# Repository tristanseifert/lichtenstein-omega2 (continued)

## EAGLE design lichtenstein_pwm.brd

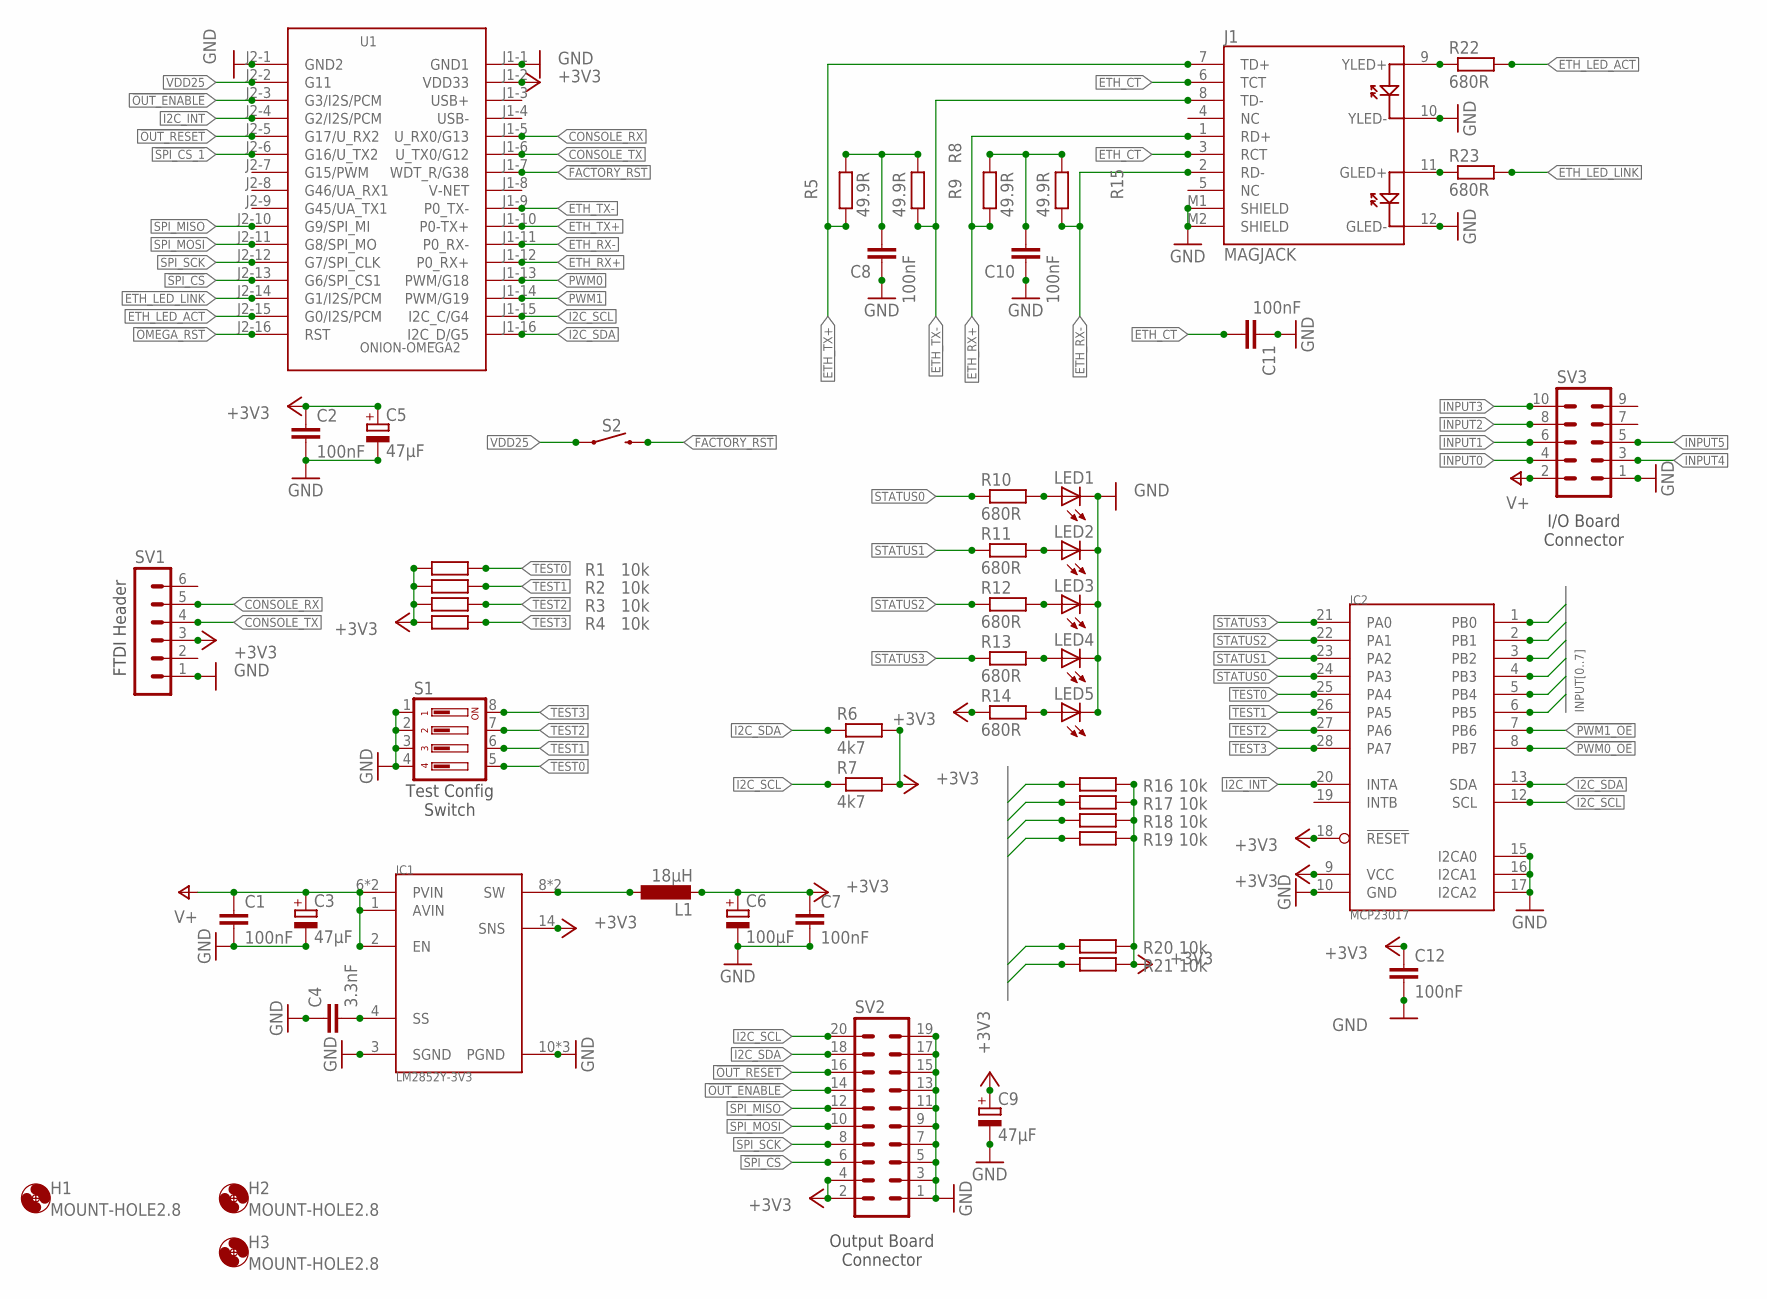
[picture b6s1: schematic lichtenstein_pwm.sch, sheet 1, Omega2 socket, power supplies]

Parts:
C1, C2, C7, C8, C10, C11, C12: 100nF; C0805; MOUSER 710-885012207072
C3, C5: 47µF; CT7343; MOUSER 581-TAJD476M016RNJV
C4: 3.3nF; C0805; MOUSER 710-885012207089
C6: 100µF; CT7343; MOUSER 581-NOSD107M006
C9: 47µF; SMC_D; MOUSER 581-TAJD476M016RNJV
H1, H2, H3: MOUNT-HOLE2.8; 2,8
IC1: LM2852Y-3V3; HTSSOP14
IC2: MCP23017; SSOP28
J1: MAGJACK
L1: 18µH; SRR1050A
LED1: LEDCHIPLED_1206; CHIPLED_1206; MOUSER 604-APTR3216SRCPRV
LED2, LED3, LED4, LED5: LEDCHIPLED_1206; CHIPLED_1206; MOUSER 604-APTR3216SGC
R1, R2, R3, R4, R16, R17, R18, R19, R20, R21: 10k; M0805; MOUSER 652-CR0805FX-1002ELF
R5, R9, R15: 49.9R; M0805; MOUSER 652-CR0805FX-49R9ELF
R6, R7: 4k7; M0805; MOUSER 652-CR0805-FX4701GLF
R8: 49.9R; M0805; MOUSER 652-CR0805-FX4701GLF
R10, R11, R12, R13, R14, R22, R23: 680R; M0805; MOUSER 652-CR0805-FX6800GLF
S1: 219-04; CTS-219-04; MOUSER 774-219-4LPS
S2: MOMENTARY-SWITCH-SPST-PTH-6.0MM; TACTILE_SWITCH_PTH_6.0MM; MOUSER 612-TL1105B
SV1: MA06-1
SV2: MA10-2; MOUSER 517-30320-6002
SV3: MA05-2; MOUSER 517-30310-6002
U1: ONION-OMEGA2; ONION-2MM-2X16; MOUSER 353-OM-O2P

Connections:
!FACTORY_RST: S2.3 (2), U1.J1-7 (WDT_R/G38)
!OMEGA_RST: U1.J2-16 (RST)
!OUT_ENABLE: SV2.14, U1.J2-3 (G3/I2S/PCM)
!OUT_RESET: SV2.16, U1.J2-5 (G17/U_RX2)
!PWM0_OE: IC2.8 (PB7); also elsewhere on the board
!PWM1_OE: IC2.7 (PB6); also elsewhere on the board
!SPI_CS: SV2.6, U1.J2-13 (G6/SPI_CS1)
!SPI_CS_1: U1.J2-6 (G16/U_TX2)
+3V3: C2.1, C5.+, C6.+, C7.1, C9.+, C12.1, IC1.14 (SNS), IC2.9 (VCC), IC2.18 (!RESET), L1.P$2 (2), R1.1, R2.1, R3.1, R4.1, R6.2, R7.2, R14.1, R16.2, R17.2, R18.2, R19.2, R20.2, R21.2, SV1.3, SV2.2, SV2.4, U1.J1-2 (VDD33); also elsewhere on the board
CONSOLE_RX: SV1.5, U1.J1-5 (U_RX0/G13)
CONSOLE_TX: SV1.4, U1.J1-6 (U_TX0/G12)
ETH_CT: C11.2, J1.3 (RCT), J1.6 (TCT)
ETH_LED_ACT: R22.2, U1.J2-15 (G0/I2S/PCM)
ETH_LED_LINK: R23.2, U1.J2-14 (G1/I2S/PCM)
ETH_RX+: J1.1 (RD+), R9.1, U1.J1-12 (P0_RX+)
ETH_RX-: J1.2 (RD-), R15.1, U1.J1-11 (P0_RX-)
ETH_TX+: J1.7 (TD+), R5.1, U1.J1-10 (P0-TX+)
ETH_TX-: J1.8 (TD-), R8.1, U1.J1-9 (P0_TX-)
GND: C1.2, C2.2, C3.-, C4.1, C5.-, C6.-, C7.2, C8.1, C9.-, C10.1, C11.1, C12.2, IC1.3 (SGND), IC1.10 (PGND), IC1.11 (PGND), IC1.PAD (PGND), IC2.10 (GND), IC2.15 (I2CA0), IC2.16 (I2CA1), IC2.17 (I2CA2), J1.10 (YLED-), J1.12 (GLED-), J1.M1 (SHIELD), J1.M2 (SHIELD), LED1.C, LED2.C, LED3.C, LED4.C, LED5.C, S1.1, S1.2, S1.3, S1.4, SV1.1, SV2.1, SV2.3, SV2.5, SV2.7, SV2.9, SV2.11, SV2.13, SV2.15, SV2.17, SV2.19, SV3.1, U1.J1-1 (GND1), U1.J2-1 (GND2); also elsewhere on the board
I2C_INT: IC2.20 (INTA), U1.J2-4 (G2/I2S/PCM)
I2C_SCL: IC2.12 (SCL), R7.1, SV2.20, U1.J1-15 (I2C_C/G4); also elsewhere on the board
I2C_SDA: IC2.13 (SDA), R6.1, SV2.18, U1.J1-16 (I2C_D/G5); also elsewhere on the board
INPUT0: IC2.2 (PB1), R16.1, SV3.4
INPUT1: IC2.4 (PB3), R17.1, SV3.6
INPUT2: IC2.6 (PB5), R20.1, SV3.8
INPUT3: IC2.5 (PB4), R21.1, SV3.10
INPUT4: IC2.1 (PB0), R18.1, SV3.3
INPUT5: IC2.3 (PB2), R19.1, SV3.5
unnamed: LED5.A, R14.2
unnamed: LED1.A, R10.2
unnamed: C8.2, R5.2, R8.2
unnamed: J1.9 (YLED+), R22.1
unnamed: J1.11 (GLED+), R23.1
unnamed: C10.2, R9.2, R15.2
unnamed: IC1.8 (SW), IC1.9 (SW), L1.P$1 (1)
unnamed: C4.2, IC1.4 (SS)
unnamed: LED2.A, R11.2
unnamed: LED3.A, R12.2
unnamed: LED4.A, R13.2
PWM0: U1.J1-13 (PWM/G18); also elsewhere on the board
PWM1: U1.J1-14 (PWM/G19); also elsewhere on the board
SPI_MISO: SV2.12, U1.J2-10 (G9/SPI_MI)
SPI_MOSI: SV2.10, U1.J2-11 (G8/SPI_MO)
SPI_SCK: SV2.8, U1.J2-12 (G7/SPI_CLK)
STATUS0: IC2.24 (PA3), R10.1
STATUS1: IC2.23 (PA2), R11.1
STATUS2: IC2.22 (PA1), R12.1
STATUS3: IC2.21 (PA0), R13.1
TEST0: IC2.25 (PA4), R1.2, S1.5
TEST1: IC2.26 (PA5), R2.2, S1.6
TEST2: IC2.27 (PA6), R3.2, S1.7
TEST3: IC2.28 (PA7), R4.2, S1.8
V+: C1.1, C3.+, IC1.1 (AVIN), IC1.2 (EN), IC1.6 (PVIN), IC1.7 (PVIN), SV3.2; also elsewhere on the board
VDD25: S2.1, U1.J2-2 (G11)

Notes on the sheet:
FTDI Header
I/O Board Connector
Test Config Switch
Output Board Connector

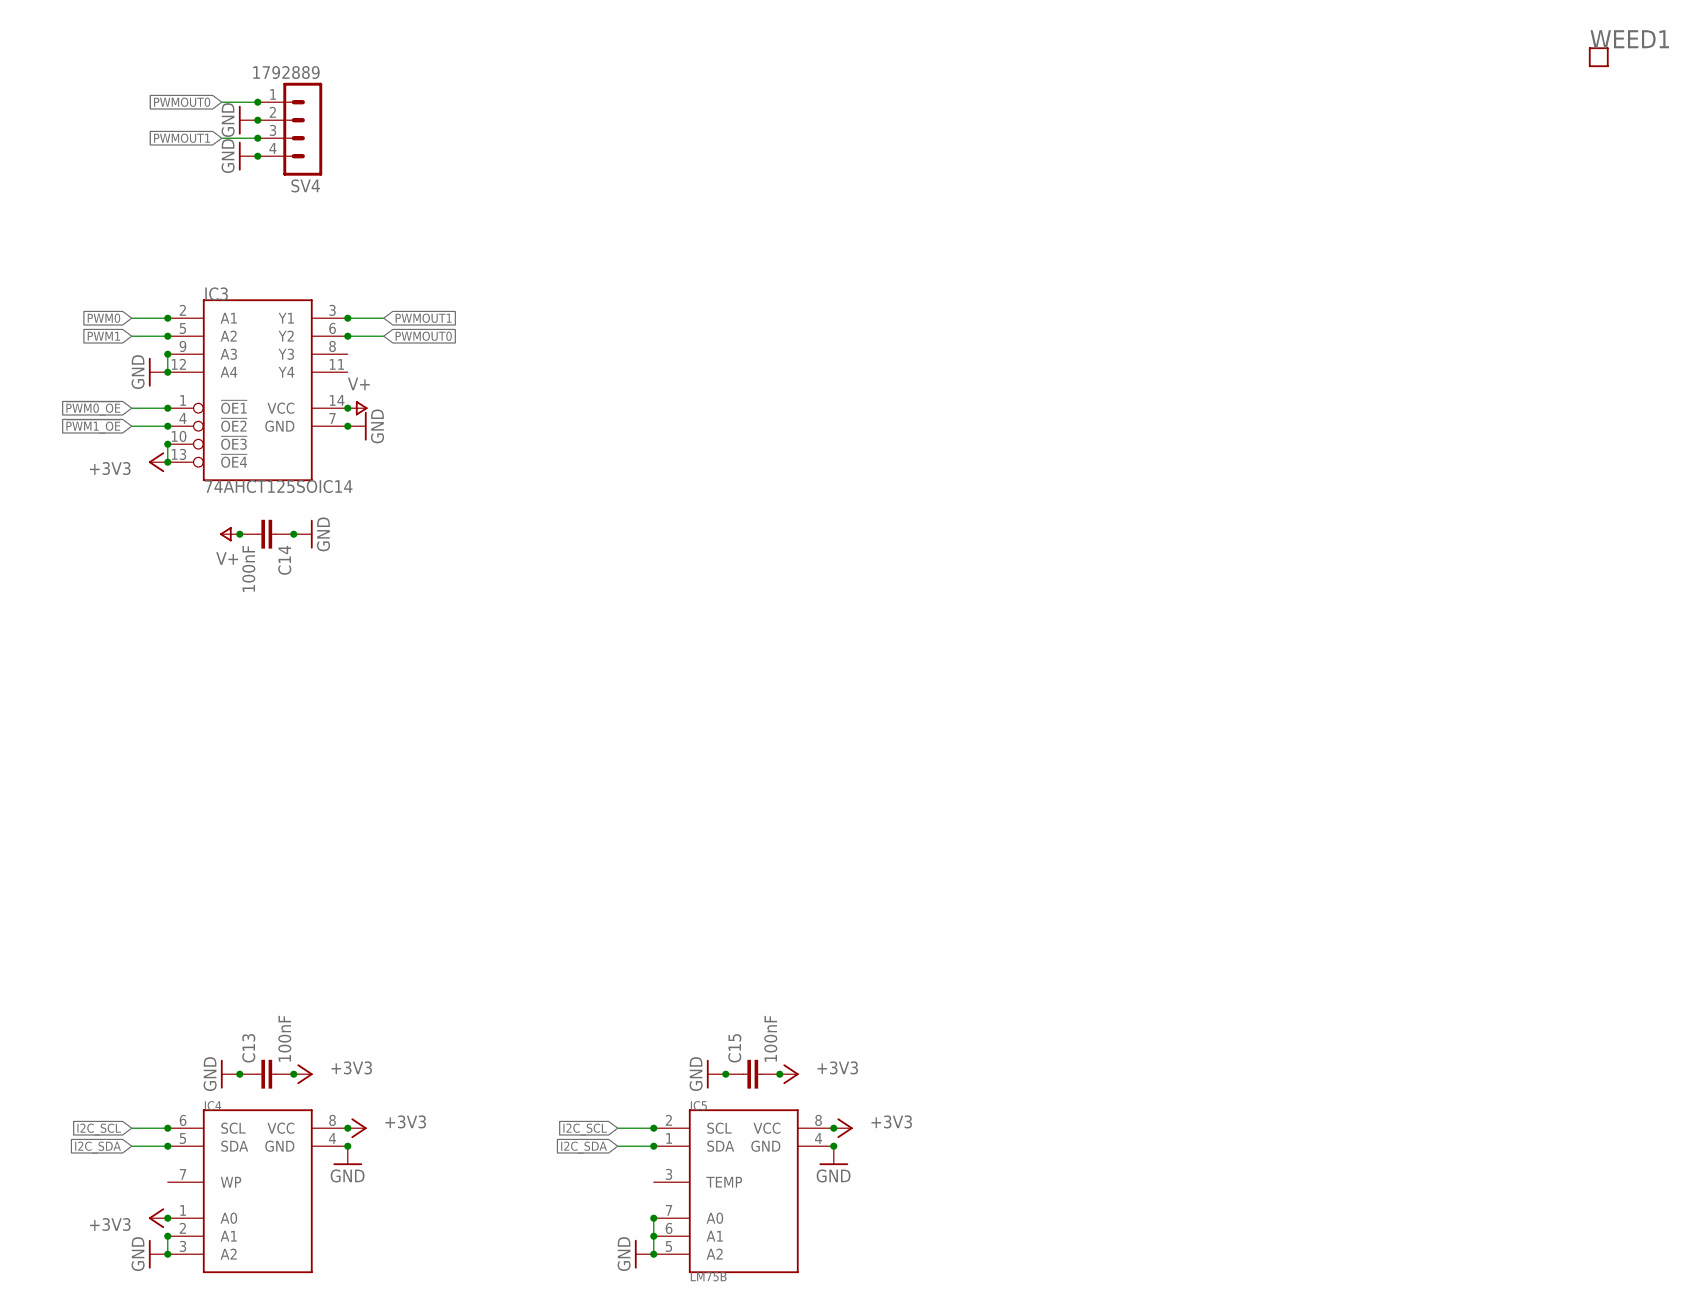
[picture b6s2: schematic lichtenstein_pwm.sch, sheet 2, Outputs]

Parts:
C13, C14, C15: 100nF; C0805; MOUSER 710-885012207072
IC3: 74AHCT125SOIC14; SO14
IC4: AT24C02DSOIC-8; SOIC8
IC5: LM75B; SOIC8
SV4: 1792889
WEED1: WEED; DOINK

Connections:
!PWM0_OE: IC3.1 (!OE1); also elsewhere on the board
!PWM1_OE: IC3.4 (!OE2); also elsewhere on the board
+3V3: C13.2, C15.2, IC3.10 (!OE3), IC3.13 (!OE4), IC4.1 (A0), IC4.8 (VCC), IC5.8 (VCC); also elsewhere on the board
GND: C13.1, C14.1, C15.1, IC3.7 (GND), IC3.9 (A3), IC3.12 (A4), IC4.2 (A1), IC4.3 (A2), IC4.4 (GND), IC5.4 (GND), IC5.5 (A2), IC5.6 (A1), IC5.7 (A0), SV4.2, SV4.4; also elsewhere on the board
I2C_SCL: IC4.6 (SCL), IC5.2 (SCL); also elsewhere on the board
I2C_SDA: IC4.5 (SDA), IC5.1 (SDA); also elsewhere on the board
PWM0: IC3.2 (A1); also elsewhere on the board
PWM1: IC3.5 (A2); also elsewhere on the board
PWMOUT0: IC3.6 (Y2), SV4.1
PWMOUT1: IC3.3 (Y1), SV4.3
V+: C14.2, IC3.14 (VCC); also elsewhere on the board

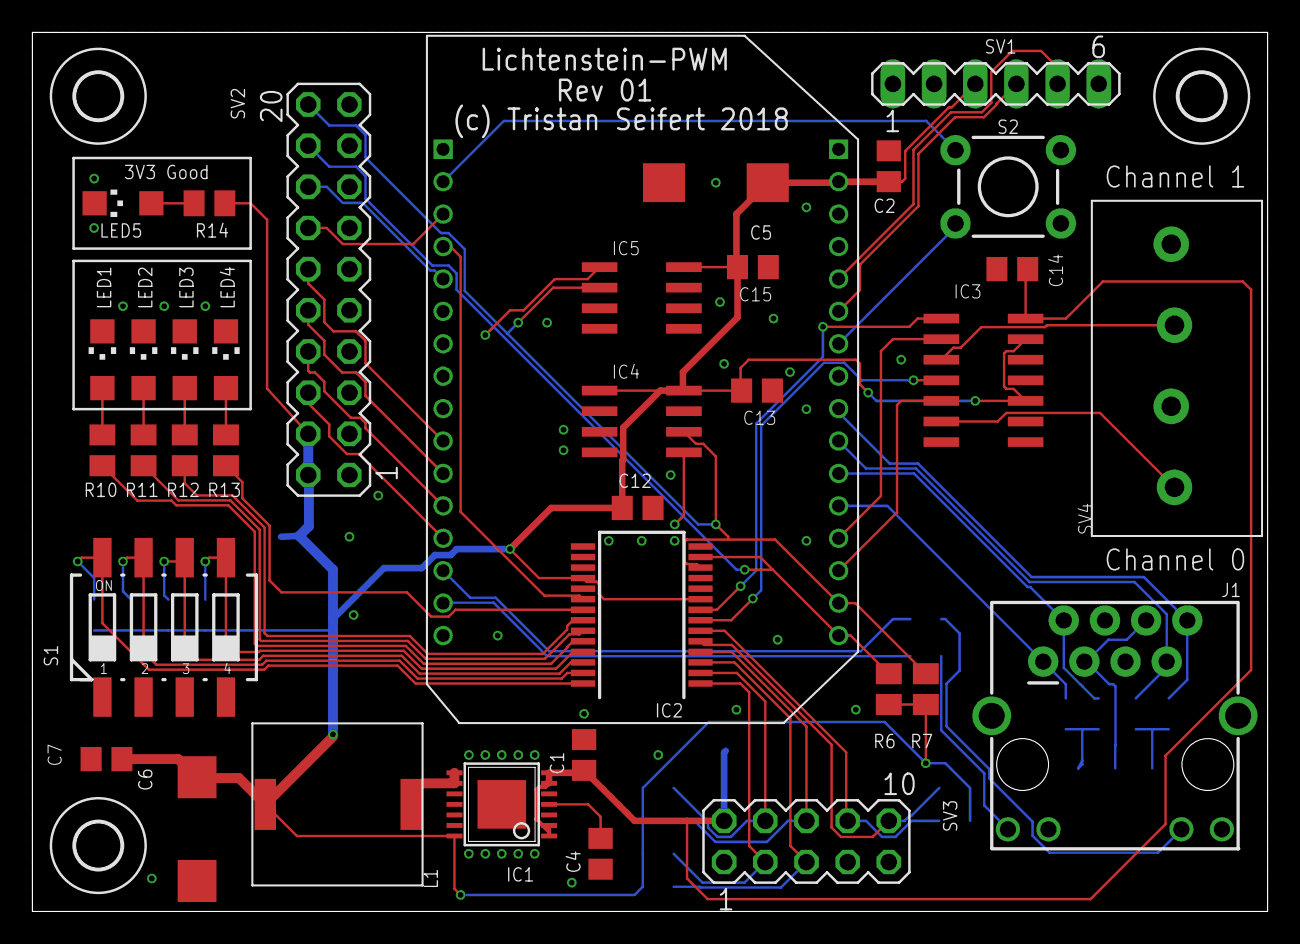
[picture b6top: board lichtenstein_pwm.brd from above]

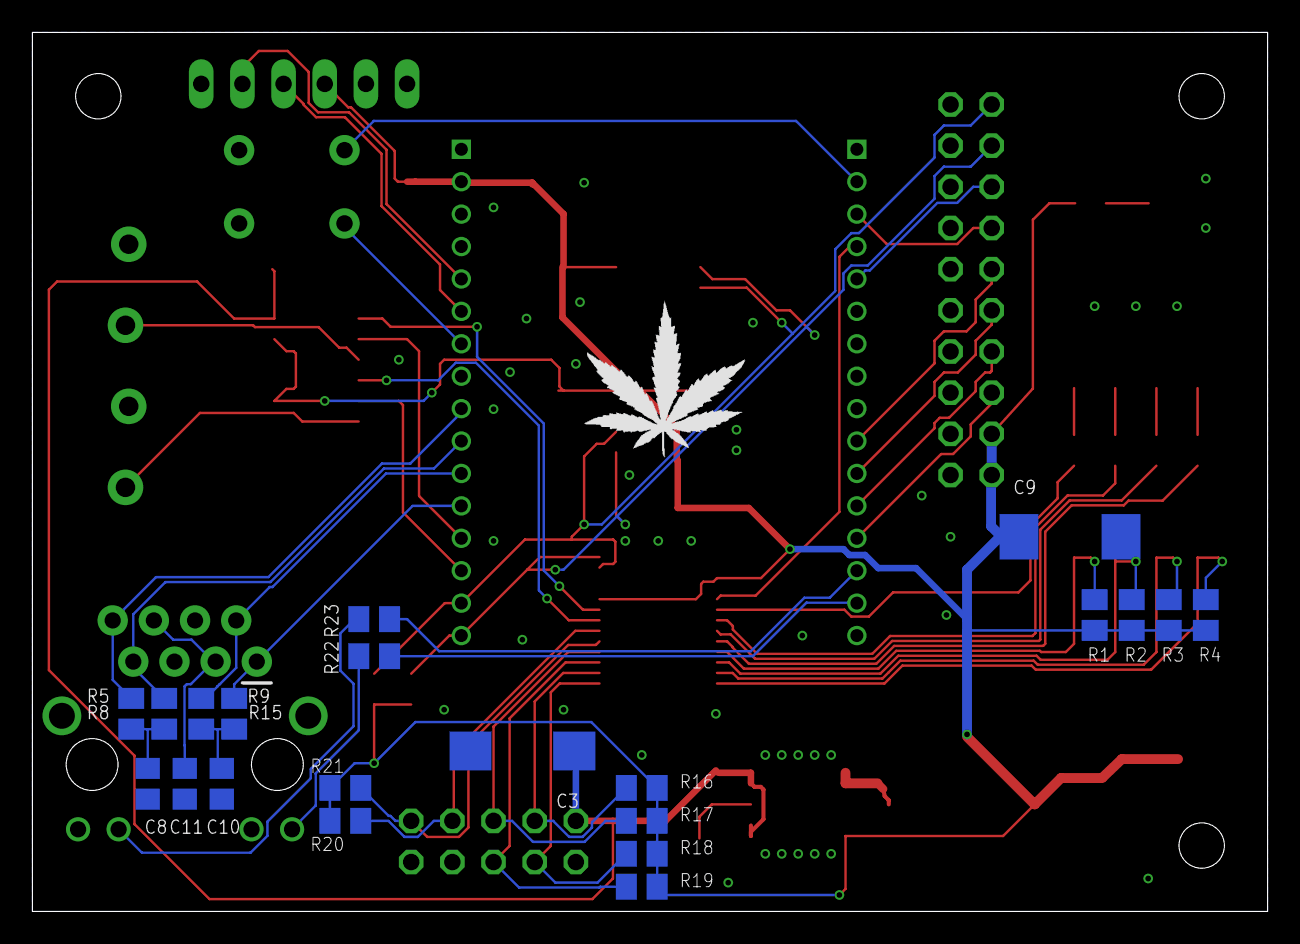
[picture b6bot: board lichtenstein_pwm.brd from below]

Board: 2 copper layers, 76.2 x 54.2 mm, 61 parts (22 on the bottom side), 54 nets.

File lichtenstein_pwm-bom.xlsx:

Partlist exported from /Users/tristan/EAGLE/lichtenstein-omega2/lichtenstein_on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
Part | Value | Device | Package | Description | MOUSER | PROD_ID | SF_ID
C1 | 100nF | C-EUC0805 | C0805 | CAPACITOR, European symbol | 710-885012207072
C2 | 100nF | C-EUC0805 | C0805 | CAPACITOR, European symbol | 710-885012207072
C3 | 47µF | CPOL-EUCT7343 | CT7343 | POLARIZED CAPACITOR, European symbol | 581-TAJD476M016RNJV
C4 | 3.3nF | C-EUC0805 | C0805 | CAPACITOR, European symbol | 710-885012207089
C5 | 47µF | CPOL-EUCT7343 | CT7343 | POLARIZED CAPACITOR, European symbol | 581-TAJD476M016RNJV
C6 | 100µF | CPOL-EUCT7343 | CT7343 | POLARIZED CAPACITOR, European symbol | 581-NOSD107M006
C7 | 100nF | C-EUC0805 | C0805 | CAPACITOR, European symbol | 710-885012207072
C8 | 100nF | C-EUC0805 | C0805 | CAPACITOR, European symbol | 710-885012207072
C9 | 47µF | CPOL-EUSMCD | SMC_D | POLARIZED CAPACITOR, European symbol | 581-TAJD476M016RNJV
C10 | 100nF | C-EUC0805 | C0805 | CAPACITOR, European symbol | 710-885012207072
C11 | 100nF | C-EUC0805 | C0805 | CAPACITOR, European symbol | 710-885012207072
C12 | 100nF | C-EUC0805 | C0805 | CAPACITOR, European symbol | 710-885012207072
C13 | 100nF | C-EUC0805 | C0805 | CAPACITOR, European symbol | 710-885012207072
C14 | 100nF | C-EUC0805 | C0805 | CAPACITOR, European symbol | 710-885012207072
C15 | 100nF | C-EUC0805 | C0805 | CAPACITOR, European symbol | 710-885012207072
H1 | MOUNT-HOLE2.8 | MOUNT-HOLE2.8 | 2,8 | MOUNTING HOLE with drill center marker
H2 | MOUNT-HOLE2.8 | MOUNT-HOLE2.8 | 2,8 | MOUNTING HOLE with drill center marker
H3 | MOUNT-HOLE2.8 | MOUNT-HOLE2.8 | 2,8 | MOUNTING HOLE with drill center marker
IC1 | LM2852Y-3V3 | LM2852HTSSOP14 | HTSSOP14 | 2A 500/1500kHz Synchronous Buck Regulator | 926-LM2852YMXA33NOPB
IC2 | MCP23017 | MCP23017SSOP28 | SSOP28 |  | 579-MCP23017T-E/SS
IC3 | 74AHCT125SOIC14 | 74AHCT125SOIC14 | SO14 | UADRUPLE BUS BUFFER GATES WITH 3-STATE OUTPUTS | 595-SN74AHCT125D
IC4 |  | AT24C02DSOIC-8 | SOIC8 | I2C-Compatible (2-wire) Serial EEPROM; 1-Kbit (128 x 8) or 2-Kbit (256 x 8) | 556-AT24C02D-SSHM-T
IC5 | LM75B | LM75B | SOIC8 | Digital temperature sensor and thermal watchdog | 771-LM75BD118
J1 | MAGJACK | MAGJACK | MAGJACK | MAGJACK: RJ-45 with LEDs |  | CONN-09556 | PRT-08534
L1 | 18µH | SRR1050A | SRR1050A | SRR1050A Series - Shielded Power Inductors | 652-SRR1050A-180Y
LED1 |  | LEDCHIPLED_1206 | CHIPLED_1206 | LED | 604-APTR3216SRCPRV
LED2 |  | LEDCHIPLED_1206 | CHIPLED_1206 | LED | 604-APTR3216SGC
LED3 |  | LEDCHIPLED_1206 | CHIPLED_1206 | LED | 604-APTR3216SGC
LED4 |  | LEDCHIPLED_1206 | CHIPLED_1206 | LED | 604-APTR3216SGC
LED5 |  | LEDCHIPLED_1206 | CHIPLED_1206 | LED | 604-APTR3216SGC
R1 | 10k | R-EU_M0805 | M0805 | RESISTOR, European symbol | 652-CR0805FX-1002ELF
R2 | 10k | R-EU_M0805 | M0805 | RESISTOR, European symbol | 652-CR0805FX-1002ELF
R3 | 10k | R-EU_M0805 | M0805 | RESISTOR, European symbol | 652-CR0805FX-1002ELF
R4 | 10k | R-EU_M0805 | M0805 | RESISTOR, European symbol | 652-CR0805FX-1002ELF
R5 | 49.9R | R-EU_M0805 | M0805 | RESISTOR, European symbol | 652-CR0805FX-49R9ELF
R6 | 4k7 | R-EU_M0805 | M0805 | RESISTOR, European symbol | 652-CR0805-FX4701GLF
R7 | 4k7 | R-EU_M0805 | M0805 | RESISTOR, European symbol | 652-CR0805-FX4701GLF
R8 | 49.9R | R-EU_M0805 | M0805 | RESISTOR, European symbol | 652-CR0805-FX4701GLF
R9 | 49.9R | R-EU_M0805 | M0805 | RESISTOR, European symbol | 652-CR0805FX-49R9ELF
R10 | 680R | R-EU_M0805 | M0805 | RESISTOR, European symbol | 652-CR0805-FX6800GLF
R11 | 680R | R-EU_M0805 | M0805 | RESISTOR, European symbol | 652-CR0805-FX6800GLF
R12 | 680R | R-EU_M0805 | M0805 | RESISTOR, European symbol | 652-CR0805-FX6800GLF
R13 | 680R | R-EU_M0805 | M0805 | RESISTOR, European symbol | 652-CR0805-FX6800GLF
R14 | 680R | R-EU_M0805 | M0805 | RESISTOR, European symbol | 652-CR0805-FX6800GLF
R15 | 49.9R | R-EU_M0805 | M0805 | RESISTOR, European symbol | 652-CR0805FX-49R9ELF
R16 | 10k | R-EU_M0805 | M0805 | RESISTOR, European symbol | 652-CR0805FX-1002ELF
R17 | 10k | R-EU_M0805 | M0805 | RESISTOR, European symbol | 652-CR0805FX-1002ELF
R18 | 10k | R-EU_M0805 | M0805 | RESISTOR, European symbol | 652-CR0805FX-1002ELF
R19 | 10k | R-EU_M0805 | M0805 | RESISTOR, European symbol | 652-CR0805FX-1002ELF
R20 | 10k | R-EU_M0805 | M0805 | RESISTOR, European symbol | 652-CR0805FX-1002ELF
R21 | 10k | R-EU_M0805 | M0805 | RESISTOR, European symbol | 652-CR0805FX-1002ELF
R22 | 680R | R-EU_M0805 | M0805 | RESISTOR, European symbol | 652-CR0805-FX6800GLF
R23 | 680R | R-EU_M0805 | M0805 | RESISTOR, European symbol | 652-CR0805-FX6800GLF
S1 | 219-04 | 219-04 | CTS-219-04 | Surface Mount DIP Switch Series 219 SMT | 774-219-4LPS
S2 |  | MOMENTARY-SWITCH-SPST-PTH-6.0MM | TACTILE_SWITCH_PTH_6.0MM | Momentary Switch (Pushbutton) - SPST | 612-TL1105B
SV1 |  | MA06-1 | MA06-1 | PIN HEADER
SV2 |  | MA10-2 | MA10-2 | PIN HEADER | 517-30320-6002
SV3 |  | MA05-2 | MA05-2 | PIN HEADER | 517-30310-6002
SV4 | 1792889 | 1792889 | 1792889 |  | 651-1792889
U1 | ONION-OMEGA2 | ONION-OMEGA2 | ONION-2MM-2X16 | Onion Omega | 353-OM-O2P
WEED1 | WEED | WEED | DOINK

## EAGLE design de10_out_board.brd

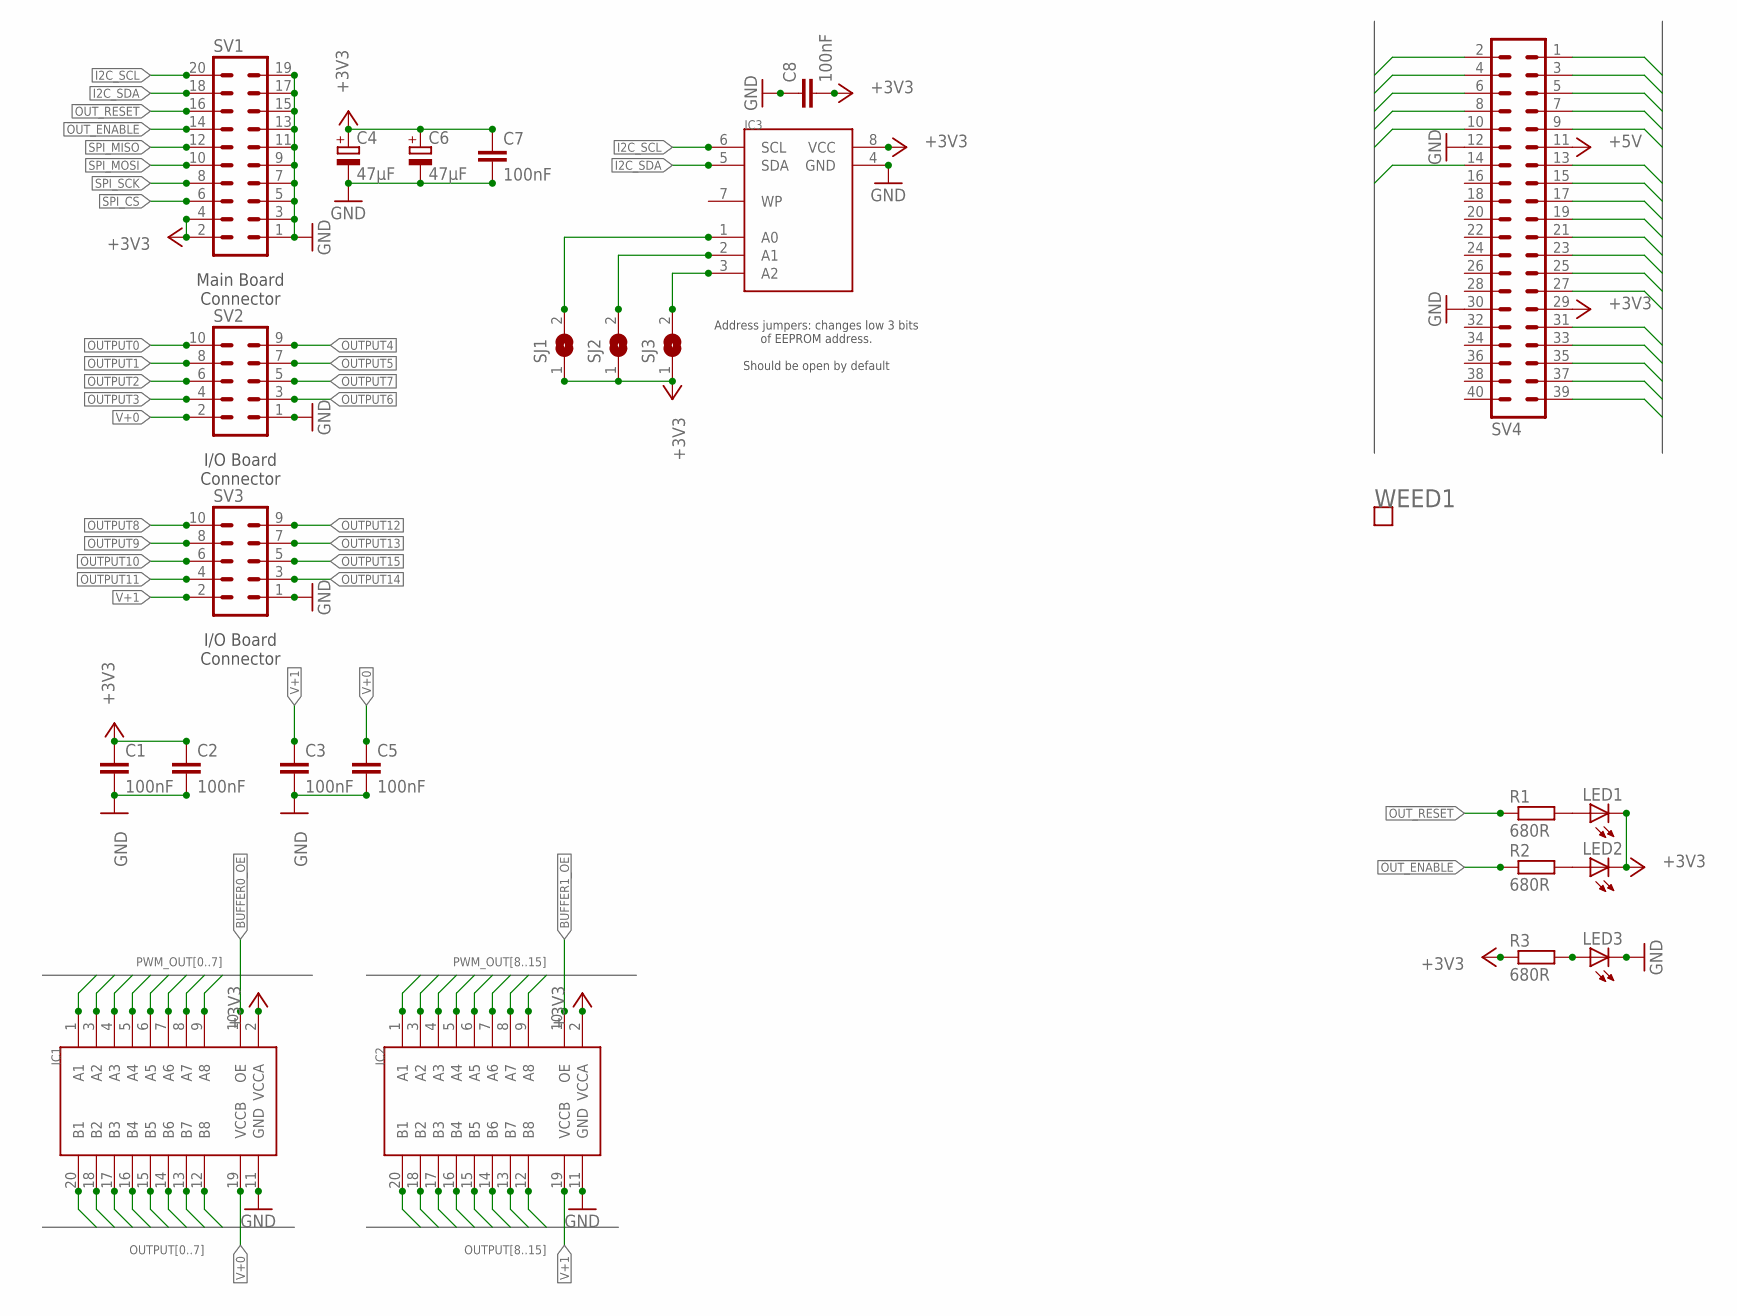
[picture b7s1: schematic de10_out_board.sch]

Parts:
C1, C2, C3, C5, C7, C8: 100nF; C0805; MOUSER 710-885012207072
C4, C6: 47µF; CT7343; MOUSER 581-TAJD476M016RNJV
IC1, IC2: TXB0108TSSOP20; TSSOP20
IC3: AT24C02DSOIC-8; SOIC8
LED1, LED2, LED3: LEDCHIPLED_1206; CHIPLED_1206; MOUSER 604-APTR3216SGC
R1, R2, R3: 680R; M0805; MOUSER 652-CR0805-FX6800GLF
SJ1, SJ2, SJ3: SJ
SV1: MA10-2; MOUSER 517-30320-6002
SV2, SV3: MA05-2; MOUSER 517-30310-6002
SV4: MA20-2
WEED1: WEED; DOINK

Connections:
!OUT_ENABLE: R2.1, SV1.14, SV4.10
!OUT_RESET: R1.1, SV1.16, SV4.14
!SPI_CS: SV1.6, SV4.2
+3V3: C1.1, C2.1, C4.+, C6.+, C7.1, C8.2, IC1.2 (VCCA), IC2.2 (VCCA), IC3.8 (VCC), LED1.C, LED2.C, R3.1, SJ1.1, SJ2.1, SJ3.1, SV1.2, SV1.4, SV4.29
+5V: SV4.11
BUFFER0_OE: IC1.10 (OE), SV4.21
BUFFER1_OE: IC2.10 (OE), SV4.1
GND: C1.2, C2.2, C3.2, C4.-, C5.2, C6.-, C7.2, C8.1, IC1.11 (GND), IC2.11 (GND), IC3.4 (GND), LED3.C, SV1.1, SV1.3, SV1.5, SV1.7, SV1.9, SV1.11, SV1.13, SV1.15, SV1.17, SV1.19, SV2.1, SV3.1, SV4.12, SV4.30
I2C_SCL: IC3.6 (SCL), SV1.20
I2C_SDA: IC3.5 (SDA), SV1.18
unnamed: LED2.A, R2.2
unnamed: LED1.A, R1.2
unnamed: LED3.A, R3.2
unnamed: IC3.3 (A2), SJ3.2
unnamed: IC3.2 (A1), SJ2.2
unnamed: IC3.1 (A0), SJ1.2
OUTPUT0: IC1.20 (B1), SV2.10
OUTPUT1: IC1.18 (B2), SV2.8
OUTPUT2: IC1.17 (B3), SV2.6
OUTPUT3: IC1.16 (B4), SV2.4
OUTPUT4: IC1.15 (B5), SV2.9
OUTPUT5: IC1.14 (B6), SV2.7
OUTPUT6: IC1.13 (B7), SV2.3
OUTPUT7: IC1.12 (B8), SV2.5
OUTPUT8: IC2.20 (B1), SV3.10
OUTPUT9: IC2.18 (B2), SV3.8
OUTPUT10: IC2.17 (B3), SV3.6
OUTPUT11: IC2.16 (B4), SV3.4
OUTPUT12: IC2.15 (B5), SV3.9
OUTPUT13: IC2.14 (B6), SV3.7
OUTPUT14: IC2.13 (B7), SV3.3
OUTPUT15: IC2.12 (B8), SV3.5
PWM_OUT0: IC1.9 (A8), SV4.23
PWM_OUT1: IC1.8 (A7), SV4.25
PWM_OUT2: IC1.7 (A6), SV4.27
PWM_OUT3: IC1.6 (A5), SV4.31
PWM_OUT4: IC1.5 (A4), SV4.33
PWM_OUT5: IC1.4 (A3), SV4.35
PWM_OUT6: IC1.3 (A2), SV4.37
PWM_OUT7: IC1.1 (A1), SV4.39
PWM_OUT8: IC2.9 (A8), SV4.3
PWM_OUT9: IC2.8 (A7), SV4.5
PWM_OUT10: IC2.7 (A6), SV4.7
PWM_OUT11: IC2.6 (A5), SV4.9
PWM_OUT12: IC2.5 (A4), SV4.13
PWM_OUT13: IC2.4 (A3), SV4.15
PWM_OUT14: IC2.3 (A2), SV4.17
PWM_OUT15: IC2.1 (A1), SV4.19
SPI_MISO: SV1.12, SV4.8
SPI_MOSI: SV1.10, SV4.6
SPI_SCK: SV1.8, SV4.4
V+0: C5.1, IC1.19 (VCCB), SV2.2
V+1: C3.1, IC2.19 (VCCB), SV3.2

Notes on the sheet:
Main Board Connector
I/O Board Connector
Address jumpers: changes low 3 bits of EEPROM address. Should be open by default

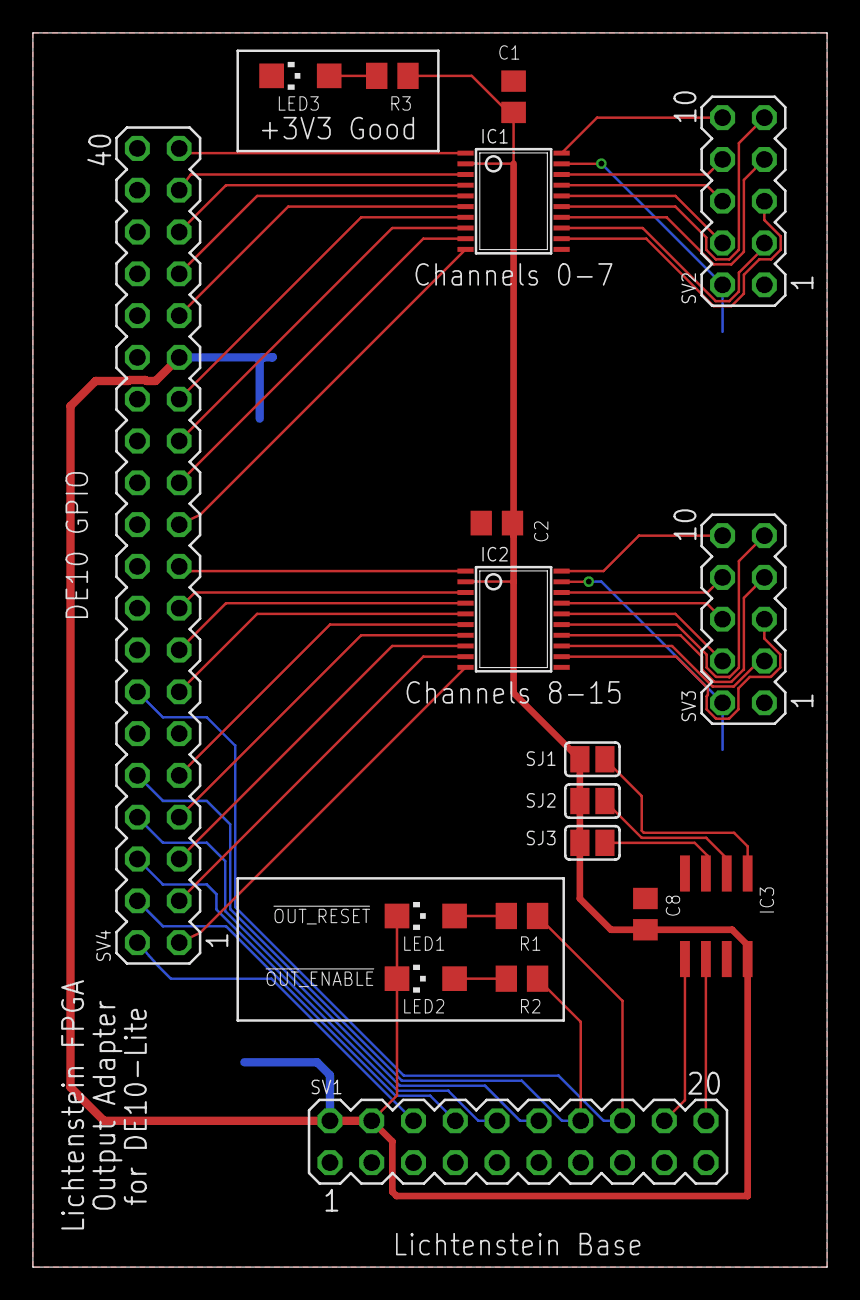
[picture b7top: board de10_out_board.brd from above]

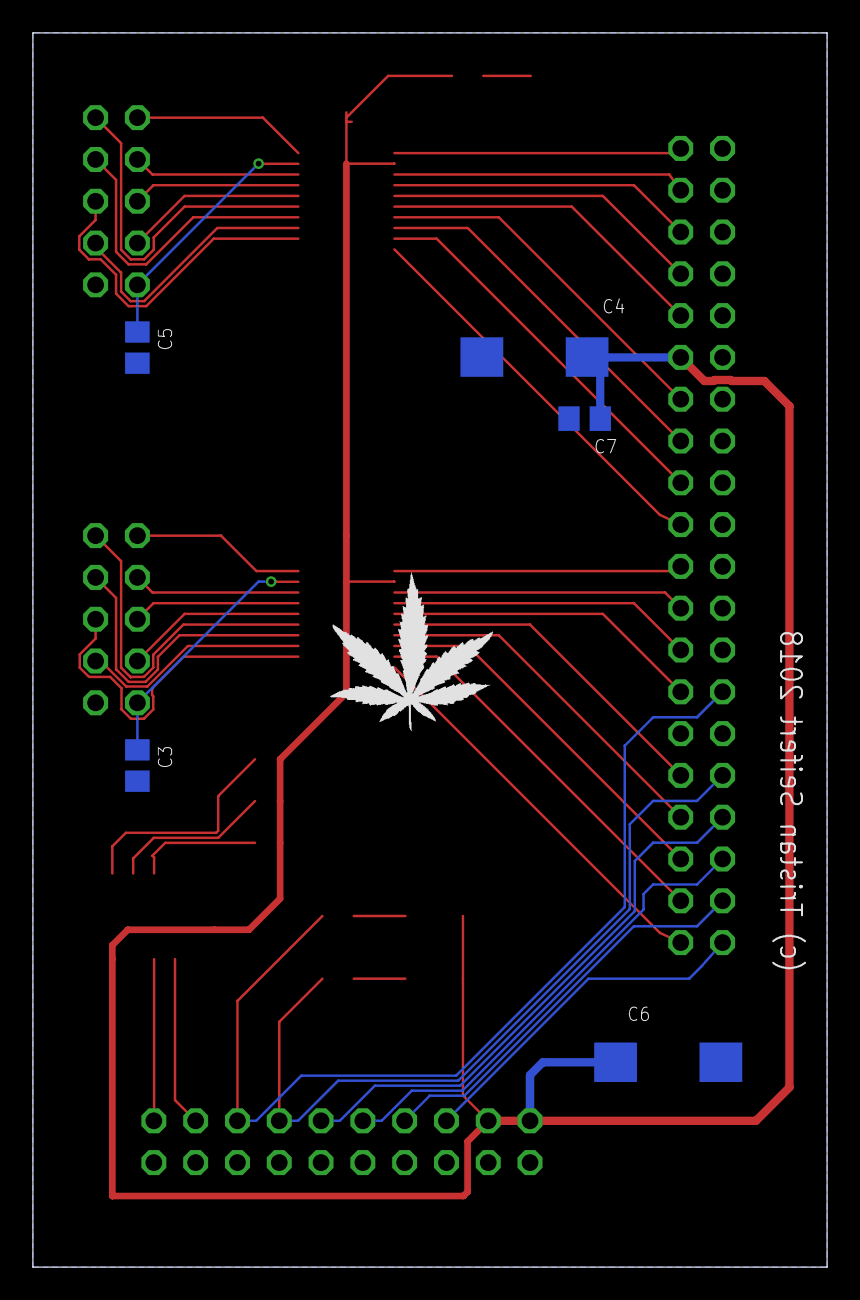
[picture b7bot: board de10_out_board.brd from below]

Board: 2 copper layers, 48.3 x 75.0 mm, 25 parts (6 on the bottom side), 52 nets.
